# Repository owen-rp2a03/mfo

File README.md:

# mfo
Multi Frequency Oscillator with 5 or 3.3 volt supply

This design has not been tested yet. Though, the board should be functionally the same; refer to the following links.

[original post about mfo](https://immerhax.com/?p=111)

[original oshpark page](https://oshpark.com/shared_projects/6oHbyT4x)

Parts: 
- U1 1.8V LDO Regulator, here a TPS78218 (Mouser P/N: 595-TPS78218DDCT)
- U2 Texas Instruments CDCE925 (Mouser P/N: 595-CDCE925PWR)
- U3 3.3V LDO Regulator, here a TLV75733 (Mouser P/N: 595-TLV75733PDYDR)
- C1 1uF 0603 SMD capacitor
- C2 1uF 0603 SMD capacitor
- C3 1uF 0603 SMD capacitor
- C4 1uF 0603 SMD capacitor
- C5 1uF 0603 SMD capacitor
- C6 1uF 0603 SMD capacitor
- R1 10K 0603 SMD resistor
- R2 10K 0603 SMD resistor
- R3 18R 0603 SMD resistor (or whatever needed to accomodate signal to the circuit)
- R4 18R 0603 SMD resistor (or whatever needed to accomodate signal to the circuit)
- Y1 27MHz crystal (Mouser P/N: 774-ATS270BSM-1E or the shallower 815-ABLS3-27MD4YFT)

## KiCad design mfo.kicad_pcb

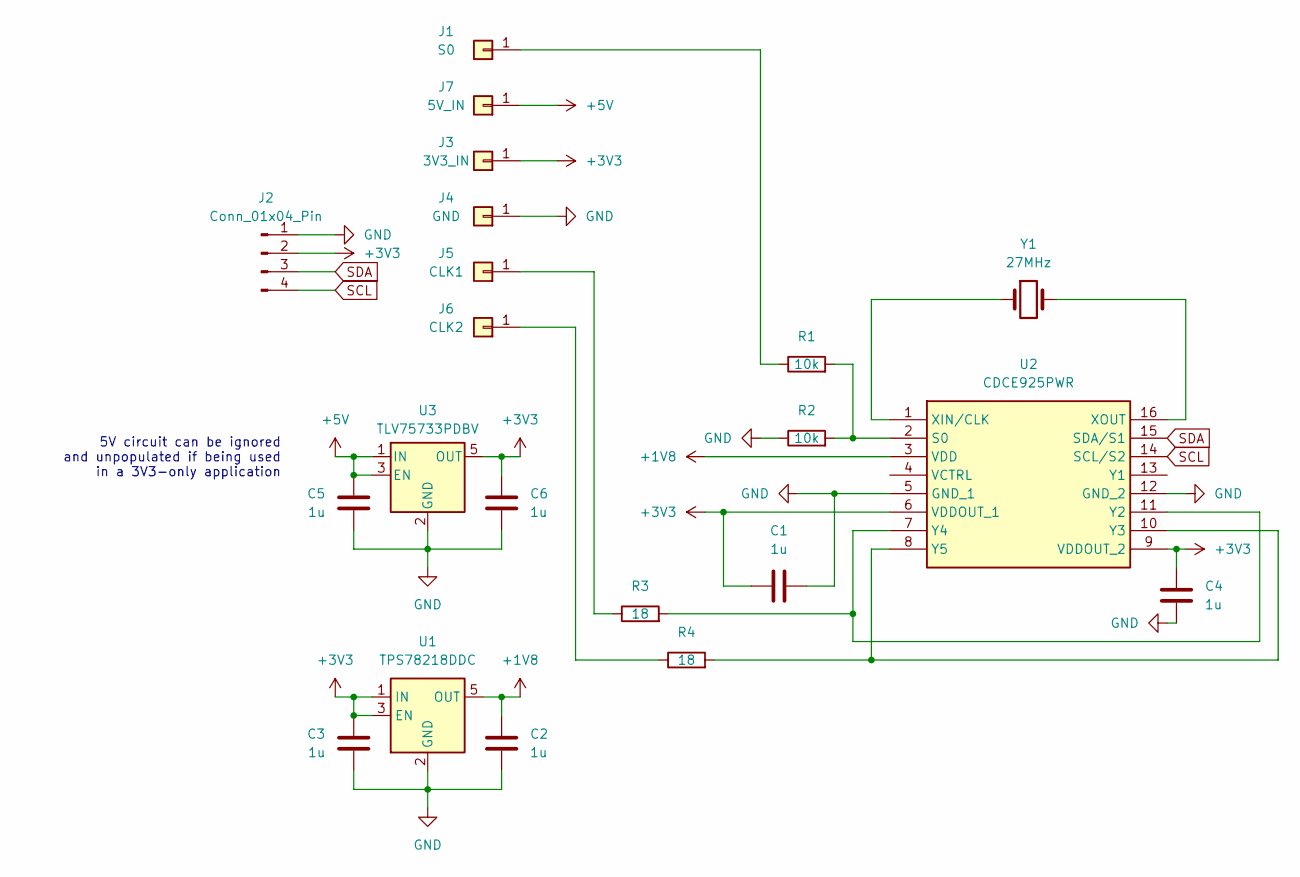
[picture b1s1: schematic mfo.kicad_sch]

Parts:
C1, C2, C3, C4, C5, C6: 1u
J1: S0
J2: Conn_01x04_Pin
J3: 3V3_IN
J4: GND
J5: CLK1
J6: CLK2
J7: 5V_IN
R1, R2: 10k
R3, R4: 18
U1: TPS78218DDC; SOT-23-5
U2: CDCE925PWR; SOP65P640X120-16N; Mouser Part Number 595-CDCE925PWR
U3: TLV75733PDBV; SOT-23-5
Y1: 27MHz

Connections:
+1V8: C2.1, U1.5 (OUT), U2.3 (VDD)
+3V3: C1.1, C3.1, C4.1, C6.1, J2.2, J3.1, U1.1 (IN), U1.3 (EN), U2.6 (VDDOUT_1), U2.9 (VDDOUT_2), U3.5 (OUT)
+5V: C5.1, J7.1, U3.1 (IN), U3.3 (EN)
GND: C1.2, C2.2, C3.2, C4.2, C5.2, C6.2, J2.1, J4.1, R2.1, U1.2 (GND), U1.4 (GND), U2.5 (GND_1), U2.12 (GND_2), U3.2 (GND)
unnamed: J1.1, R1.1
unnamed: J5.1, R3.1
unnamed: J6.1, R4.1
unnamed: R1.2, R2.2, U2.2 (S0)
unnamed: U2.1 (XIN/CLK), Y1.1
unnamed: U2.16 (XOUT), Y1.2
unnamed: R3.2, U2.7 (Y4), U2.11 (Y2)
unnamed: R4.2, U2.8 (Y5), U2.10 (Y3)
SCL: J2.4, U2.14 (SCL/S2)
SDA: J2.3, U2.15 (SDA/S1)

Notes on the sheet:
5V circuit can be ignored and unpopulated if being used in a 3V3-only application

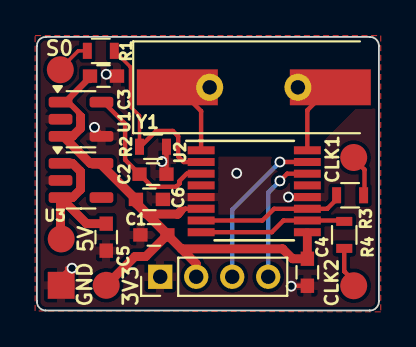
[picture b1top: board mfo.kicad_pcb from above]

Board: 2 copper layers, 19.0 x 15.2 mm, 21 parts (0 on the bottom side), 14 nets.

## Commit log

2026-05-16 add gerbers
2026-05-17 files for programming
2026-05-17 rename
